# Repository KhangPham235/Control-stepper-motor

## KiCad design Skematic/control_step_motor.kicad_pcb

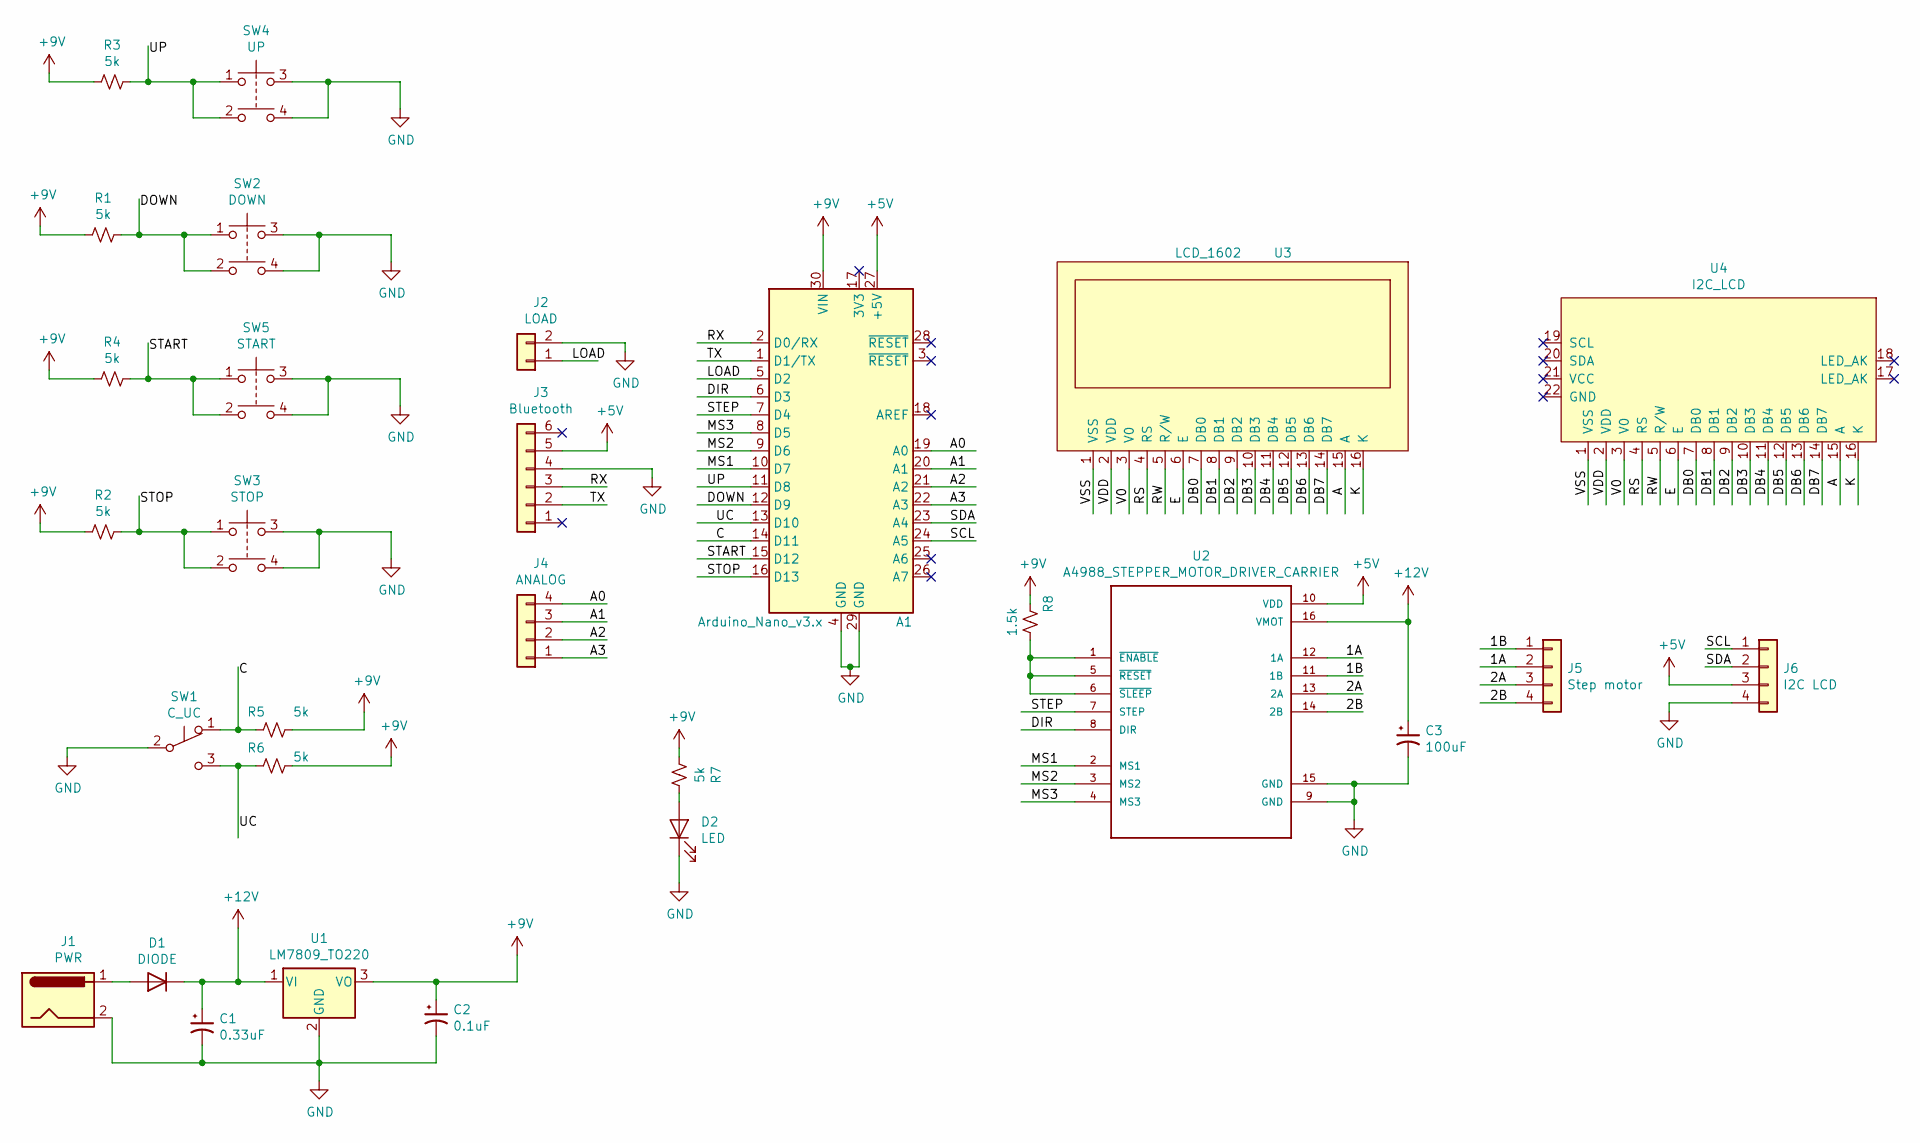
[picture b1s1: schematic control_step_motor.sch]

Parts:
A1: Arduino_Nano_v3.x; Arduino_Nano
C1: 0.33uF; CP_Radial_D5.0mm_P2.50mm
C2: 0.1uF; CP_Radial_D5.0mm_P2.50mm
C3: 100uF; CP_Radial_D8.0mm_P3.50mm
D1: DIODE; D_A-405_P10.16mm_Horizontal
D2: LED; LED_D5.0mm
J1: PWR; BarrelJack_Horizontal
J2: LOAD; PinSocket_1x02_P2.54mm_Vertical
J3: Bluetooth; PinSocket_1x06_P2.54mm_Vertical
J4: ANALOG; PinSocket_1x04_P2.54mm_Vertical
J5: Step motor; JST_XH_B4B-XH-A_1x04_P2.50mm_Vertical
J6: I2C LCD; JST_XH_B4B-XH-A_1x04_P2.50mm_Vertical
R1, R2, R3, R4, R5, R6, R7: 5k; R_Axial_DIN0207_L6.3mm_D2.5mm_P7.62mm_Horizontal
R8: 1.5k; R_Axial_DIN0207_L6.3mm_D2.5mm_P7.62mm_Horizontal
SW1: C_UC; Button_OFO
SW2: DOWN; SW_TH_Tactile_Omron_B3F-10xx
SW3: STOP; SW_TH_Tactile_Omron_B3F-10xx
SW4: UP; SW_TH_Tactile_Omron_B3F-10xx
SW5: START; SW_TH_Tactile_Omron_B3F-10xx
U1: LM7809_TO220; TO-220-3_Vertical
U2: A4988_STEPPER_MOTOR_DRIVER_CARRIER; A4988_Driver
U3: LCD_1602
U4: I2C_LCD

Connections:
+5V: A1.27 (+5V), J3.5, J6.3, U2.10 (VDD)
+9V: A1.30 (VIN), C2.1, R1.2, R2.2, R3.2, R4.2, R5.1, R6.1, R7.2, R8.2, U1.3 (VO)
+12V: C1.1, C3.1, D1.2 (K), U1.1 (VI), U2.16 (VMOT)
/1A: J5.2, U2.12 (1A)
/1B: J5.1, U2.11 (1B)
/2A: J5.3, U2.13 (2A)
/2B: J5.4, U2.14 (2B)
/A: U3.15 (A), U4.15 (A)
/A0: A1.19 (A0), J4.4
/A1: A1.20 (A1), J4.3
/A2: A1.21 (A2), J4.2
/A3: A1.22 (A3), J4.1
/C: A1.14 (D11), R5.2, SW1.1 (A)
/DB0: U3.7 (DB0), U4.7 (DB0)
/DB1: U3.8 (DB1), U4.8 (DB1)
/DB2: U3.9 (DB2), U4.9 (DB2)
/DB3: U3.10 (DB3), U4.10 (DB3)
/DB4: U3.11 (DB4), U4.11 (DB4)
/DB5: U3.12 (DB5), U4.12 (DB5)
/DB6: U3.13 (DB6), U4.13 (DB6)
/DB7: U3.14 (DB7), U4.14 (DB7)
/DIR: A1.6 (D3), U2.8 (DIR)
/DOWN: A1.12 (D9), R1.1, SW2.1, SW2.2
/E: U3.6 (E), U4.6 (E)
/K: U3.16 (K), U4.16 (K)
/LOAD: A1.5 (D2), J2.1
/MS1: A1.10 (D7), U2.2 (MS1)
/MS2: A1.9 (D6), U2.3 (MS2)
/MS3: A1.8 (D5), U2.4 (MS3)
/RS: U3.4 (RS), U4.4 (RS)
/RW: U3.5 (R/W), U4.5 (R/W)
/RX: A1.2 (D0/RX), J3.3
/SCL: A1.24 (A5), J6.1
/SDA: A1.23 (A4), J6.2
/START: A1.15 (D12), R4.1, SW5.1, SW5.2
/STEP: A1.7 (D4), U2.7 (STEP)
/STOP: A1.16 (D13), R2.1, SW3.1, SW3.2
/TX: A1.1 (D1/TX), J3.2
/UC: A1.13 (D10), R6.2, SW1.3 (C)
/UP: A1.11 (D8), R3.1, SW4.1, SW4.2
/V0: U3.3 (V0), U4.3 (V0)
/VDD: U3.2 (VDD), U4.2 (VDD)
/VSS: U3.1 (VSS), U4.1 (VSS)
GND: A1.4 (GND), A1.29 (GND), C1.2, C2.2, C3.2, D2.1 (K), J1.2, J2.2, J3.4, J6.4, SW1.2 (B), SW2.3, SW2.4, SW3.3, SW3.4, SW4.3, SW4.4, SW5.3, SW5.4, U1.2 (GND), U2.9 (GND), U2.15 (GND)
unnamed: D1.1 (A), J1.1
unnamed: D2.2 (A), R7.1
unnamed: R8.1, U2.1 (~ENABLE~), U2.5 (~RESET~), U2.6 (~SLEEP~)

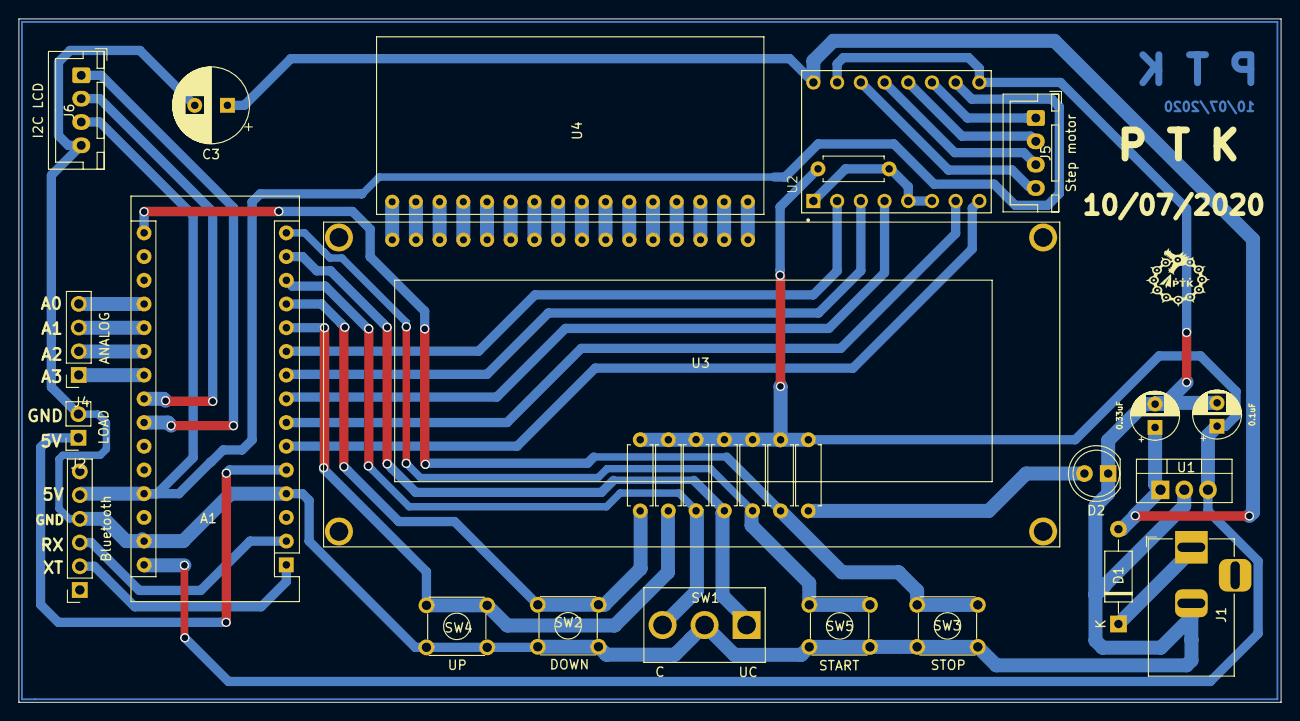
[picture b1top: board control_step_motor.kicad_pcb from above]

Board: 2 copper layers, 135.2 x 73.2 mm, 29 parts (0 on the bottom side), 47 nets.

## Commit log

2020-07-21 First update
2020-07-21 Create count_rev_stepper_motor.ino
    Code arduino to control step motor
2020-07-21 second update
